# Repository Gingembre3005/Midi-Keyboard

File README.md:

# Midi-Keyboard

## Introduction:

This is my midi keyboard that I made for the third week of the Hackclub Half Life challenge. It is ocean themed.

## Schematic:

Here is a picture of the schematics for the project. 

## PCB: 

Picture of my projects PCB. 
There are small pictures on the front and the back of the board to give the ocean vibe. 

## Picture of the front of the PCB:

## Picture of the back of the PCB:

## Firmware:

The code's main function is to react and play a sound when the user touches one of the capacitive keys (the main piano keys). 
The physical switches are here to change the octave of the notes that will be played by the capacitive keys. 

## How to flash firmware:

To flash the firmware onto the board you should follow these steps:

1. Connect the board to your computer.
2. Download CircuitPython.
3. Copy CircuitPython onto the board.
4. Save the code.py program in the board.

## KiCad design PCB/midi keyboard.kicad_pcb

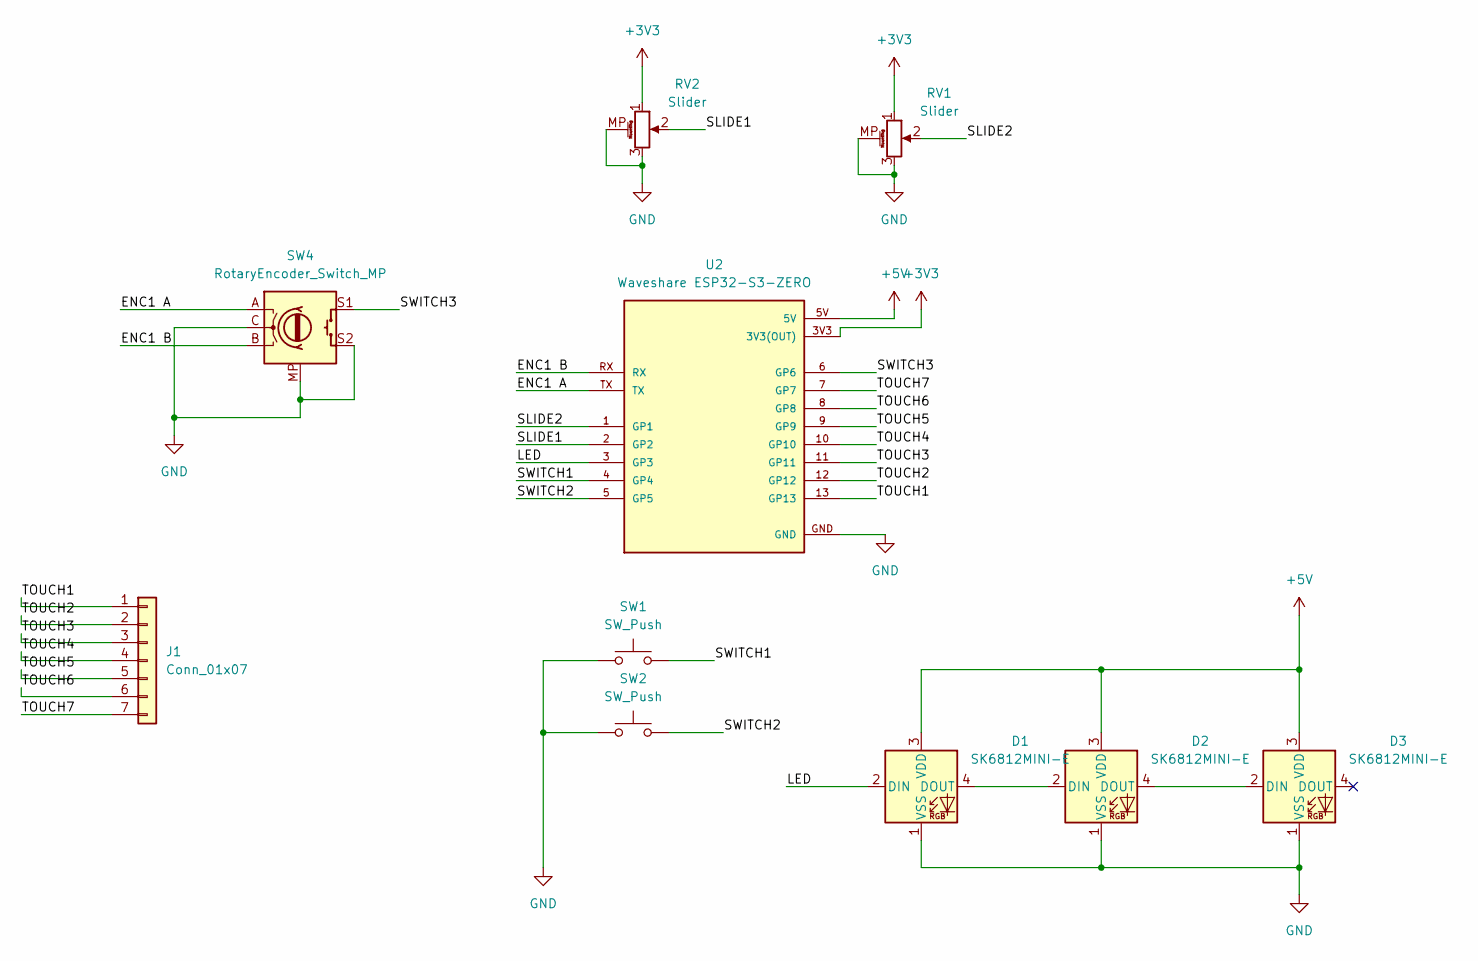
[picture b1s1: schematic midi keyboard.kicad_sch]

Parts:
D1, D2, D3: SK6812MINI-E; LED_SK6812MINI-E_3.2x2.8mm_P1.5mm_ReverseMount
J1: Conn_01x07; Capacitive Keys
RV1, RV2: Slider; Potentiometer_Bourns_PTA1543_Single_Slide
SW1, SW2: SW_Push; Kailh Choc Low-Profile Switches
SW4: RotaryEncoder_Switch_MP; RotaryEncoder_Alps_EC11E-Switch_Vertical_H20mm
U2: Waveshare ESP32-S3-ZERO; Waveshare ESP32-S3-Zero; PARTREV NA

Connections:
+3V3: RV1.1, RV2.1, U2.3V3 (3V3(OUT))
+5V: D1.3 (VDD), D2.3 (VDD), D3.3 (VDD), U2.5V
/ENC1 A: SW4.A, U2.TX
/ENC1 B: SW4.B, U2.RX
/LED: D1.2 (DIN), U2.3 (GP3)
/SLIDE1: RV2.2, U2.2 (GP2)
/SLIDE2: RV1.2, U2.1 (GP1)
/SWITCH1: SW1.2, U2.4 (GP4)
/SWITCH2: SW2.2, U2.5 (GP5)
/SWITCH3: SW4.S1, U2.6 (GP6)
/TOUCH1: J1.1, U2.13 (GP13)
/TOUCH2: J1.2, U2.12 (GP12)
/TOUCH3: J1.3, U2.11 (GP11)
/TOUCH4: J1.4, U2.10 (GP10)
/TOUCH5: J1.5, U2.9 (GP9)
/TOUCH6: J1.6, U2.8 (GP8)
/TOUCH7: J1.7, U2.7 (GP7)
GND: D1.1 (VSS), D2.1 (VSS), D3.1 (VSS), RV1.3, RV1.MP (MountPin), RV2.3, RV2.MP (MountPin), SW1.1, SW2.1, SW4.C, SW4.MP, SW4.S2, U2.GND
unnamed: D1.4 (DOUT), D2.2 (DIN)
unnamed: D2.4 (DOUT), D3.2 (DIN)

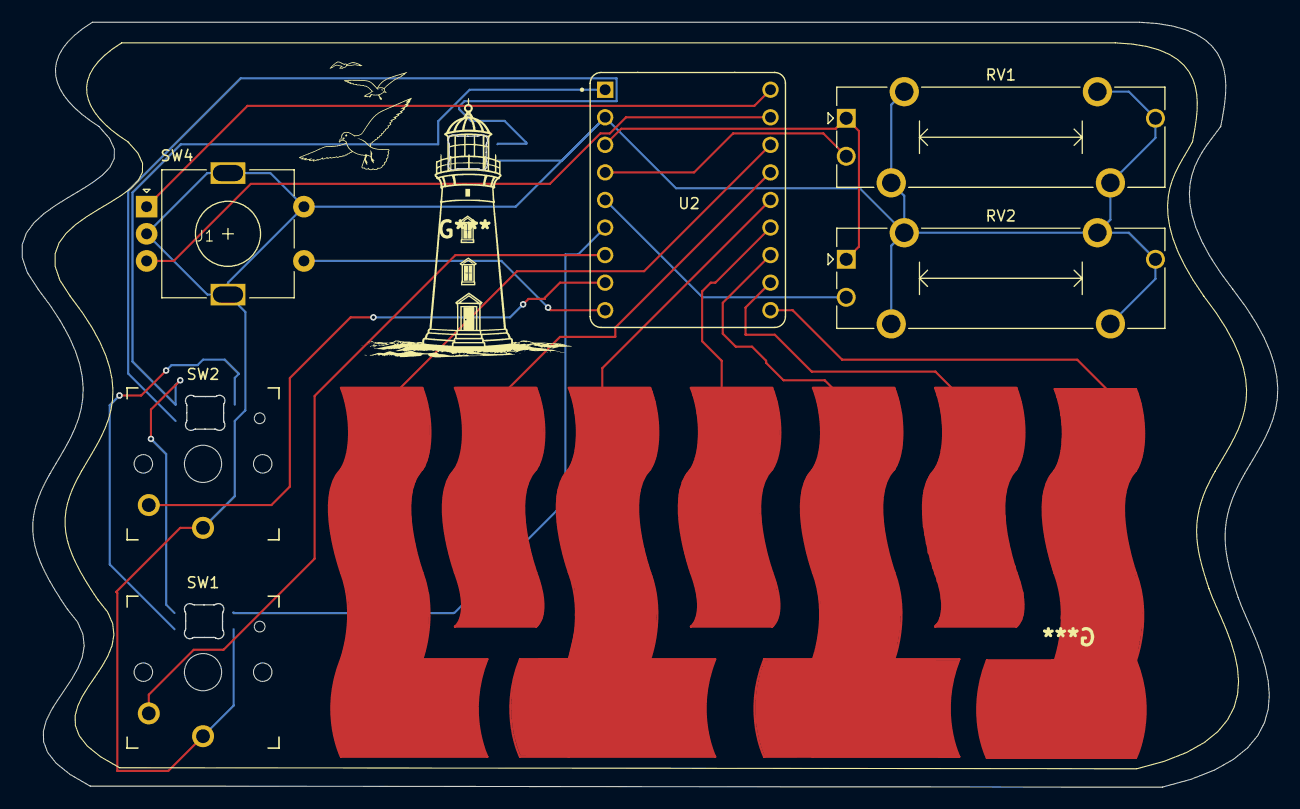
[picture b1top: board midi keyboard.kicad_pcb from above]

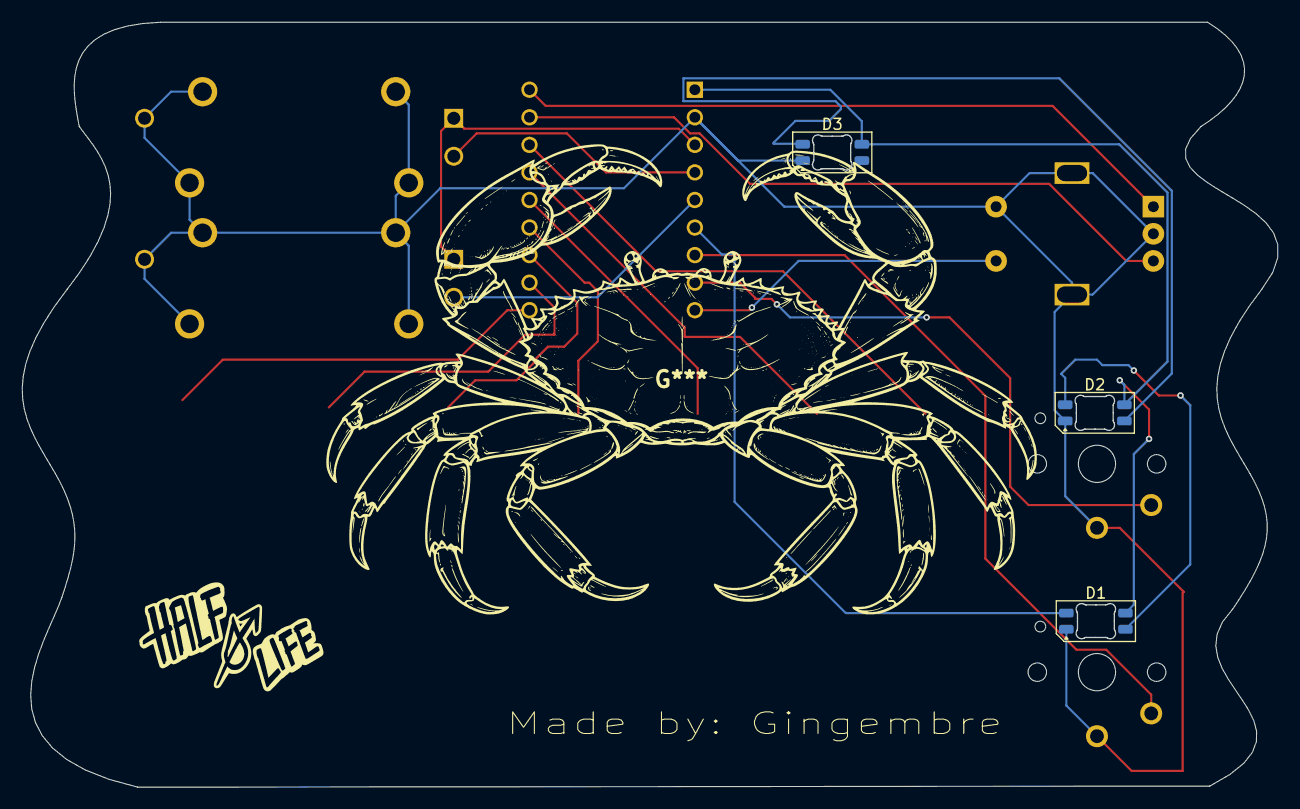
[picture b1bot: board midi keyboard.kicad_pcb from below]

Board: 2 copper layers, 115.7 x 70.5 mm, 10 parts (3 on the bottom side), 20 nets.

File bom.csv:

Designator,Footprint,Quantity,Value,LCSC Part #
"D1, D2, D3",LED_SK6812MINI-E_3.2x2.8mm_P1.5mm_ReverseMount,3,SK6812MINI-E,
J1,Capacitive Keys,1,Conn_01x07,
"RV1, RV2",Potentiometer_Bourns_PTA1543_Single_Slide,2,Slider,
"SW1, SW2",Kailh Choc Low-Profile Switches,2,SW_Push,
SW4,RotaryEncoder_Alps_EC11E-Switch_Vertical_H20mm,1,RotaryEncoder_Switch_MP,
U2,Waveshare ESP32-S3-Zero,1,Waveshare ESP32-S3-ZERO,
